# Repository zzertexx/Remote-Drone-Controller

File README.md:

# Remote Drone Controller
Remote Controller for my [Drone](https://github.com/zzertexx/drone) with FPV viewer with Phone and Control with Joystick

# How it works
My drone uses ELRS channel to Receive commands and this controller acts as Transmitter on ELRS using SX1280 module while getting joysticks commands from ESP32-C3 that sends them to ESP32-S3.

# How to use it
1. Order PCB
2. Solder all components as stated in Schematics
3. Flash [ELRS firmware](https://github.com/expresslrs/expresslrs) for the main ESP32-S3
4. Flash the companion firmware @ /firmware to the ESP32-C3
5. Power on, bind the controller to drone's ELRS receiver
6. Calibrate joystick min/center/max values.

# Why I designed it?
I designed drone recently, but I don't have controller for it, so I built one

# Bill of Materials
| Name | Quantity |
| --- | --- |
| E28-2G4M27S SX1280 module | 1 pc | 
| ESP32-S3 | 1 pc |
| ESP32-C3 | 1 pc |
| 2.4 GHz antenna  | 1 pc |
| Joystick | 2 pcs |
| TP4056 chip | 1 pc |
| FS8205A chip | 1 pc |
| DW01A chip | 1 pc |
| MT3608 5V converter | 1 pc |
| AMS1117 3.3V converter | 1 pc |
| WS2812 | 2 pcs |
| Tactile Button | 2 pcs |
| Resistors | 1K x3, 1.2K, 100, 4.7K x2, 0, 110K, 15K, 5.1K |
| Inductor 4.7uH | 1 pc |
| Capacitors | 0.1uF x2, 22uF x3, 47uF |
| LED THT D3mm | 2 pcs |
| 2400mAh Battery 18650 | 1 pc |
| Battery Holder | 1 pc |

# Next feautures
3D Enclosure
VTX Video Receiver for Phone

# Photos

# AI DISCLOSURE
AI was used for researching various components, tradeofs and their compatibility

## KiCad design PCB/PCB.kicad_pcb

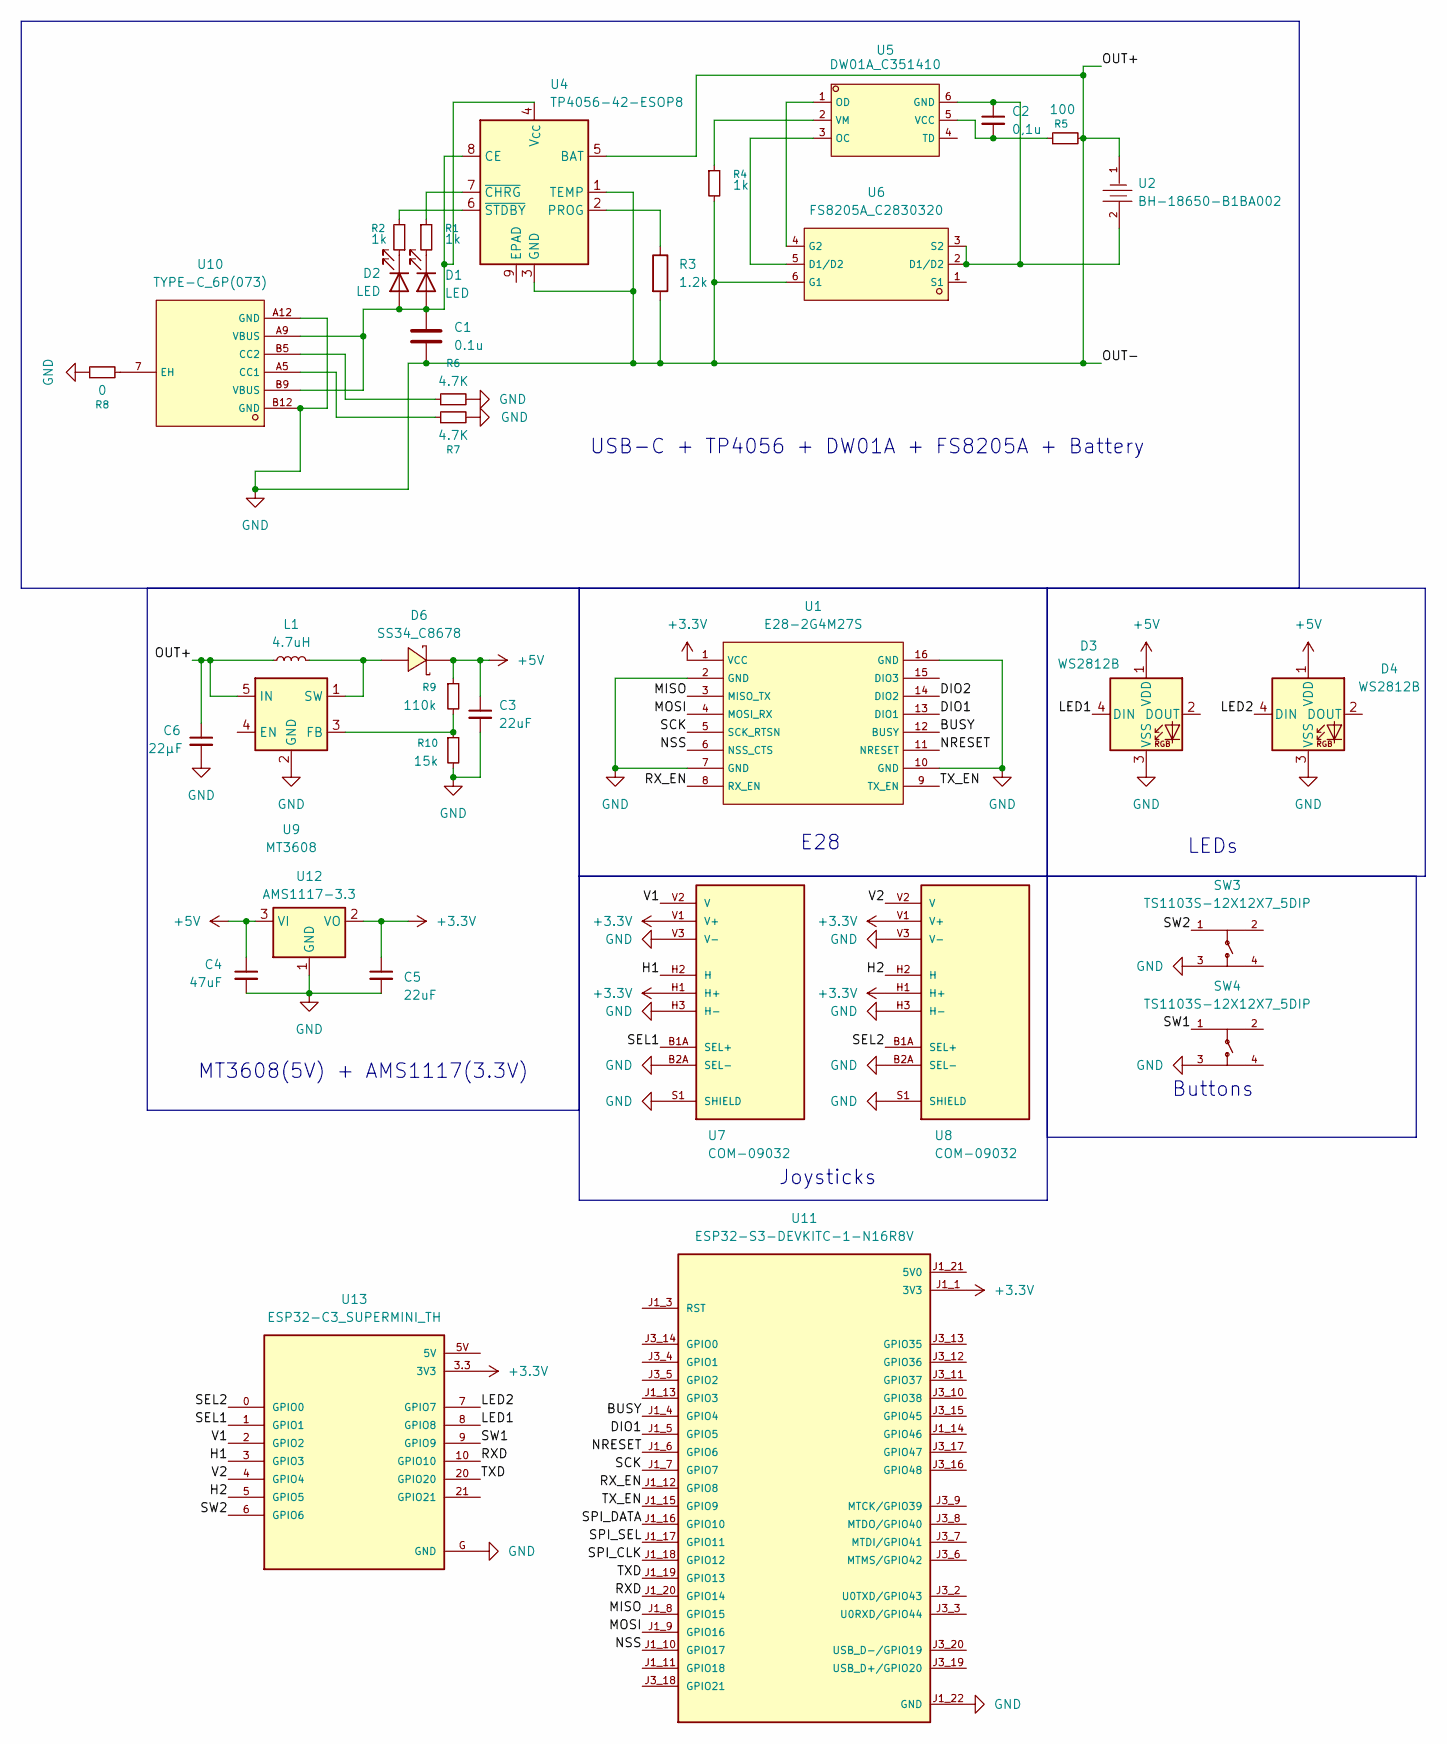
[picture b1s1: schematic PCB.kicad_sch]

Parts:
C1: 0.1u; C_0402_1005Metric
C2: 0,1u; C_0402_1005Metric
C3, C5: 22uF; C_1206_3216Metric
C4: 47uF; C_0805_2012Metric
C6: 22µF; C_1206_3216Metric
D1, D2: LED; LED_D3.0mm
D3, D4: WS2812B; LED_WS2812B_PLCC4_5.0x5.0mm_P3.2mm
D6: SS34_C8678; SMA_L4.3-W2.6-LS5.2-RD; LCSC C8678
L1: 4.7uH; C_0603_1608Metric
R1, R2, R4: 1k; C_0603_1608Metric
R3: 1.2k; C_0603_1608Metric
R5: 100; C_0603_1608Metric
R6, R7: 4.7K; C_0603_1608Metric
R8: 0; C_0603_1608Metric
R9: 110k; C_0603_1608Metric
R10: 15k; C_0603_1608Metric
SW3, SW4: TS1103S-12X12X7_5DIP; SW-TH_4P-L12.0-W12.0-P5.00-LS12.5; LCSC C48677982
U1: E28-2G4M27S; WIRELM-SMD_E28-2G4M2XS; LCSC C411312
U2: BH-18650-B1BA002; BATTERY-SMD_18650-1S-L77.1-W20.7-1; LCSC C2988620
U4: TP4056-42-ESOP8; SOIC-8-1EP_3.9x4.9mm_P1.27mm_EP2.41x3.3mm_ThermalVias
U5: DW01A_C351410; SOT-23-6_L2.9-W1.6-P0.95-LS2.8-BL; LCSC C351410
U6: FS8205A_C2830320; SOT-23-6_L2.9-W1.6-P0.95-LS2.8-BR; LCSC C2830320
U7, U8: COM-09032; XDCR_COM-09032; PARTREV N/A
U9: MT3608; SOT-23-6
U10: TYPE-C_6P(073); TYPE-C-SMD_TYPE-C-6P-073; LCSC C668623
U11: ESP32-S3-DEVKITC-1-N16R8V; XCVR_ESP32-S3-DEVKITC-1-N16R8V; PARTREV 1.1
U12: AMS1117-3.3; SOT-223-3_TabPin2
U13: ESP32-C3_SUPERMINI_TH; MODULE_ESP32-C3_SUPERMINI_TH

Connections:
+3.3V: C5.1, U1.1 (VCC), U7.H1 (H+), U7.V1 (V+), U8.H1 (H+), U8.V1 (V+), U11.J1_1 (3V3), U11.J1_2 (3V3), U12.2 (VO), U13.3.3 (3V3)
+5V: C3.1, C4.1, D3.1 (VDD), D4.1 (VDD), D6.1 (K), R9.1, U12.3 (VI)
/BUSY: U1.12 (BUSY), U11.J1_4 (GPIO4)
/DIO1: U1.13 (DIO1), U11.J1_5 (GPIO5)
/H1: U7.H2 (H), U13.3 (GPIO3); also elsewhere on the board
/H2: U8.H2 (H), U13.5 (GPIO5); also elsewhere on the board
/LED1: D3.4 (DIN), U13.8 (GPIO8); also elsewhere on the board
/LED2: D4.4 (DIN), U13.7 (GPIO7); also elsewhere on the board
/MISO: U1.3 (MISO_TX), U11.J1_8 (GPIO15)
/MOSI: U1.4 (MOSI_RX), U11.J1_9 (GPIO16)
/NRESET: U1.11 (NRESET), U11.J1_6 (GPIO6)
/NSS: U1.6 (NSS_CTS), U11.J1_10 (GPIO17)
/RXD: U11.J1_20 (GPIO14), U13.10 (GPIO10); also elsewhere on the board
/RX_EN: U1.8 (RX_EN), U11.J1_12 (GPIO8)
/SCK: U1.5 (SCK_RTSN), U11.J1_7 (GPIO7)
/SEL1: U7.B1A (SEL+), U13.1 (GPIO1); also elsewhere on the board
/SEL2: U8.B1A (SEL+), U13.0 (GPIO0); also elsewhere on the board
/SPI_CLK: U11.J1_18 (GPIO12)
/SPI_DATA: U11.J1_16 (GPIO10)
/SPI_SEL: U11.J1_17 (GPIO11)
/SW1: SW4.1, U13.9 (GPIO9); also elsewhere on the board
/SW2: SW3.1, U13.6 (GPIO6); also elsewhere on the board
/TXD: U11.J1_19 (GPIO13), U13.20 (GPIO20); also elsewhere on the board
/TX_EN: U1.9 (TX_EN), U11.J1_15 (GPIO9)
/V1: U7.V2 (V), U13.2 (GPIO2); also elsewhere on the board
/V2: U8.V2 (V), U13.4 (GPIO4); also elsewhere on the board
GND: C1.2, C3.2, C4.2, C5.2, C6.1, C6.2, D3.3 (VSS), D4.3 (VSS), L1.1, R3.2, R4.2, R5.2, R6.2, R7.2, R8.1, R10.2, SW3.3, SW4.3, U1.2 (GND), U1.7 (GND), U1.10 (GND), U1.16 (GND), U2.1, U4.1 (TEMP), U4.3 (GND), U4.5 (BAT), U6.6 (G1), U7.B2A (SEL-), U7.H3 (H-), U7.S1 (SHIELD), U7.S2 (SHIELD), U7.S3 (SHIELD), U7.S4 (SHIELD), U7.V3 (V-), U8.B2A (SEL-), U8.H3 (H-), U8.S1 (SHIELD), U8.S2 (SHIELD), U8.S3 (SHIELD), U8.S4 (SHIELD), U8.V3 (V-), U9.2 (GND), U9.5 (IN), U10.A12 (GND), U10.B12 (GND), U11.J1_22 (GND), U11.J3_1 (GND), U11.J3_21 (GND), U11.J3_22 (GND), U12.1 (GND), U13.G (GND)
unnamed: C1.1, D1.2 (A), D2.2 (A), U4.4 (V_{CC}), U4.8 (CE), U10.A9 (VBUS), U10.B9 (VBUS)
unnamed: D1.1 (K), R1.2
unnamed: D2.1 (K), R2.1
unnamed: D6.2 (A), L1.2, U9.1 (SW)
unnamed: R3.1, U4.2 (PROG)
unnamed: R1.1, U4.7 (~CHRG)
unnamed: R2.2, U4.6 (~STDBY)
unnamed: C2.1, U2.2, U5.6 (GND), U6.2 (D1/D2), U6.3 (S2)
unnamed: U5.3 (OC), U6.5 (D1/D2)
unnamed: U5.1 (OD), U6.4 (G2)
unnamed: C2.2, R5.1, U5.5 (VCC)
unnamed: R4.1, U5.2 (VM)
unnamed: R9.2, R10.1, U9.3 (FB)
unnamed: R7.1, U10.A5 (CC1)
unnamed: R6.1, U10.B5 (CC2)
unnamed: R8.2, U10.7 (EH)

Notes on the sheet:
LEDs
USB-C + TP4056 + DW01A + FS8205A + Battery
MT3608(5V) + AMS1117(3.3V)
Buttons
E28
Joysticks

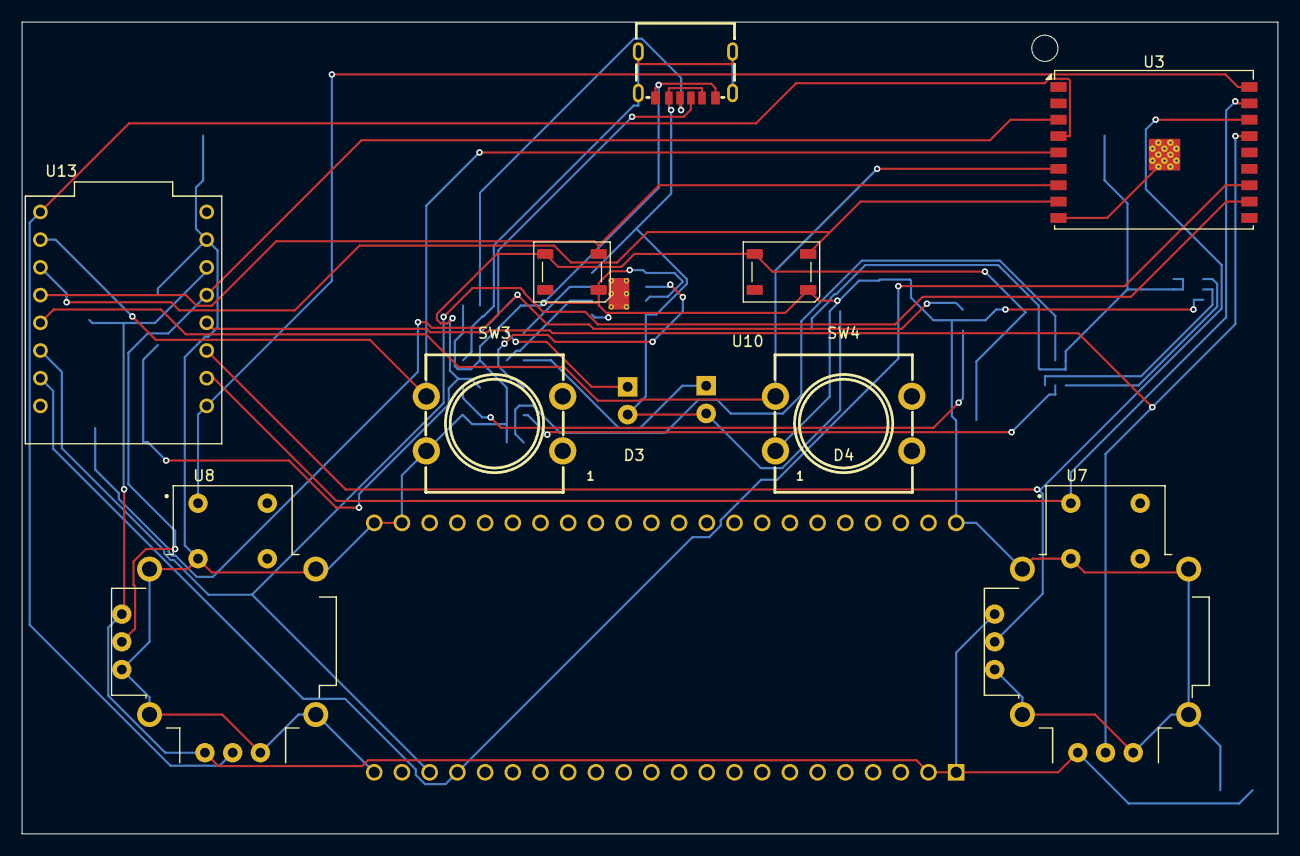
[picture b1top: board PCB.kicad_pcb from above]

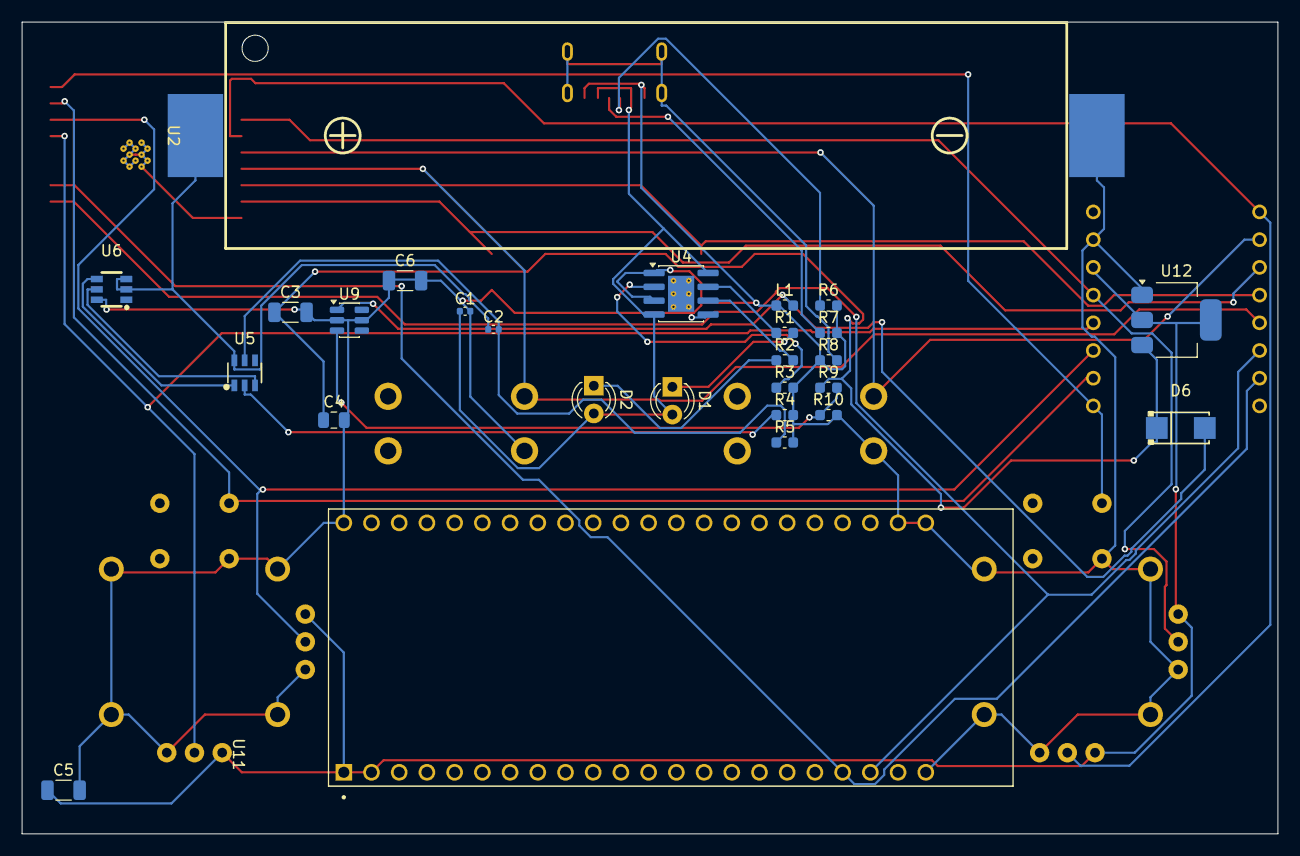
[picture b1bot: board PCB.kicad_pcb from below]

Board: 2 copper layers, 115.1 x 74.4 mm, 36 parts (27 on the bottom side), 32 nets.

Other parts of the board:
U3: ESP32-C3-WROOM-02U

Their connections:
/H1: U3.15 (IO3); also elsewhere on the board
/H2: U3.4 (IO5); also elsewhere on the board
/LED1: U3.7 (IO8); also elsewhere on the board
/LED2: U3.8 (IO9); also elsewhere on the board
/RXD: U3.11 (IO20/RXD); also elsewhere on the board
/SEL1: U3.17 (IO1); also elsewhere on the board
/SEL2: U3.18 (IO0); also elsewhere on the board
/SW1: U3.6 (IO7); also elsewhere on the board
/SW2: U3.5 (IO6); also elsewhere on the board
/TXD: U3.12 (IO21/TXD); also elsewhere on the board
/V1: U3.16 (IO2); also elsewhere on the board
/V2: U3.3 (IO4); also elsewhere on the board
unnamed: U3.9 (GND), U3.19 (GND)

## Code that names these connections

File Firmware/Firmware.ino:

#include <Adafruit_NeoPixel.h>

#define V1_PIN            0 
#define H1_PIN            1  
#define V2_PIN            2  
#define H2_PIN            3   
#define SEL2_PIN          4  
#define SW2_PIN           6  
#define LED2_PIN          7 
#define LED1_PIN          8   
#define SW1_PIN           9   
#define RXD_PIN           10  
#define TXD_PIN           20  
#define SEL1_PIN          21  

#define CRSF_BAUD         420000

#define CRSF_SYNC_BYTE                     0xC8
#define CRSF_FRAMETYPE_RC_CHANNELS_PACKED  0x16
#define CRSF_FRAMETYPE_LINK_STATISTICS     0x14
#define CRSF_CHANNEL_VALUE_MIN   172   
#define CRSF_CHANNEL_VALUE_MID   992   
#define CRSF_CHANNEL_VALUE_MAX   1811  

#define ELRS_ADDRESS          0xEE
#define ADDR_RADIO             0xEA
#define ELRS_BIND_COMMAND      0xFF
#define TYPE_SETTINGS_WRITE    0x2D

Adafruit_NeoPixel led1(1, LED1_PIN, NEO_GRB + NEO_KHZ800);
Adafruit_NeoPixel led2(1, LED2_PIN, NEO_GRB + NEO_KHZ800);

uint16_t channels[16];

uint8_t crc8_dvb_s2(uint8_t crc, uint8_t a) {
  crc ^= a;
  for (int i = 0; i < 8; i++) {
    crc = (crc & 0x80) ? (crc << 1) ^ 0xD5 : (crc << 1);
  }
  return crc;
}

uint8_t crc8_buf(uint8_t *data, uint8_t len) {
  uint8_t crc = 0;
  for (uint8_t i = 0; i < len; i++) crc = crc8_dvb_s2(crc, data[i]);
  return crc;
}

uint16_t adcToCrsf(int adcValue, int adcMin, int adcMid, int adcMax) {
  adcValue = constrain(adcValue, adcMin, adcMax);
  if (adcValue < adcMid) {
    return map(adcValue, adcMin, adcMid, CRSF_CHANNEL_VALUE_MIN, CRSF_CHANNEL_VALUE_MID);
  }
  return map(adcValue, adcMid, adcMax, CRSF_CHANNEL_VALUE_MID, CRSF_CHANNEL_VALUE_MAX);
}

void sendCrsfChannels() {
  uint8_t frame[26];
  uint8_t payload[22];
  memset(payload, 0, sizeof(payload));

  uint32_t bitBuffer = 0;
  int bitsInBuffer = 0;
  int byteIndex = 0;

  for (int ch = 0; ch < 16; ch++) {
    bitBuffer |= ((uint32_t)(channels[ch] & 0x7FF)) << bitsInBuffer;
    bitsInBuffer += 11;
    while (bitsInBuffer >= 8) {
      payload[byteIndex++] = bitBuffer & 0xFF;
      bitBuffer >>= 8;
      bitsInBuffer -= 8;
    }
  }
  if (bitsInBuffer > 0) payload[byteIndex++] = bitBuffer & 0xFF;

  frame[0] = CRSF_SYNC_BYTE;
  frame[1] = 22 + 2;
  frame[2] = CRSF_FRAMETYPE_RC_CHANNELS_PACKED;
  memcpy(&frame[3], payload, 22);
  frame[25] = crc8_buf(&frame[2], 23);

  Serial1.write(frame, 26);
}

void sendBindCommand() {
  uint8_t packet[8];
  packet[0] = ELRS_ADDRESS;
  packet[1] = 6;
  packet[2] = TYPE_SETTINGS_WRITE;
  packet[3] = ELRS_ADDRESS;
  packet[4] = ADDR_RADIO;
  packet[5] = ELRS_BIND_COMMAND;
  packet[6] = 0x01;
  packet[7] = crc8_buf(&packet[2], 5);
  Serial1.write(packet, 8);
}

void updatePowerLED() {
  led1.setPixelColor(0, led1.Color(40, 40, 40));
  led1.show();
}

volatile bool droneConnected = false;
volatile unsigned long lastTelemetryMillis = 0;
#define TELEMETRY_TIMEOUT_MS 1000

void updateConnectionLED() {
  bool connected = droneConnected && (millis() - lastTelemetryMillis < TELEMETRY_TIMEOUT_MS);
  led2.setPixelColor(0, connected ? led2.Color(0, 255, 0) : led2.Color(255, 0, 0));
  led2.show();
}

uint8_t rxBuf[64];
uint8_t rxIndex = 0;

void pollCrsfTelemetry() {
  while (Serial1.available()) {
    uint8_t b = Serial1.read();
    if (rxIndex == 0 && b != CRSF_SYNC_BYTE) continue;
    rxBuf[rxIndex++] = b;

    if (rxIndex >= 2) {
      uint8_t frameLen = rxBuf[1];
      if (rxIndex >= frameLen + 2) {
        uint8_t expectedCrc = rxBuf[frameLen + 1];
        uint8_t actualCrc = crc8_buf(&rxBuf[2], frameLen - 1);
        if (expectedCrc == actualCrc && rxBuf[2] == CRSF_FRAMETYPE_LINK_STATISTICS) {
          droneConnected = true;
          lastTelemetryMillis = millis();
        }
        rxIndex = 0;
      }
    }
    if (rxIndex >= sizeof(rxBuf)) rxIndex = 0;
  }
}

bool lastSW2State = HIGH;
bool lastSW1State = HIGH;
unsigned long sw1PressStart = 0;
#define SW1_LONGPRESS_MS 1500

void handleButtons() {
  bool sw2State = digitalRead(SW2_PIN);
  if (sw2State == LOW && lastSW2State == HIGH) {
    sendBindCommand();
  }
  lastSW2State = sw2State;

  bool sw1State = digitalRead(SW1_PIN);
  if (sw1State == LOW && lastSW1State == HIGH) {
    sw1PressStart = millis();
  }
  if (sw1State == LOW && (millis() - sw1PressStart > SW1_LONGPRESS_MS)) {
    led1.setPixelColor(0, 0); led1.show();
    led2.setPixelColor(0, 0); led2.show();
    gpio_wakeup_enable((gpio_num_t)SW1_PIN, GPIO_INTR_LOW_LEVEL);
    esp_sleep_enable_gpio_wakeup();
    esp_deep_sleep_start();
  }
  lastSW1State = sw1State;

  channels[6] = (digitalRead(SEL1_PIN) == LOW) ? CRSF_CHANNEL_VALUE_MAX : CRSF_CHANNEL_VALUE_MIN;
  channels[7] = (digitalRead(SEL2_PIN) == LOW) ? CRSF_CHANNEL_VALUE_MAX : CRSF_CHANNEL_VALUE_MIN;
}

void readJoysticks() {
  int adcMin = 100, adcMid = 2048, adcMax = 3995;

  int v1Raw = analogRead(V1_PIN);
  int h1Raw = analogRead(H1_PIN);
  int v2Raw = analogRead(V2_PIN);
  int h2Raw = analogRead(H2_PIN);

  channels[0] = adcToCrsf(h2Raw, adcMin, adcMid, adcMax); 
  channels[1] = adcToCrsf(v2Raw, adcMin, adcMid, adcMax); 
  channels[2] = adcToCrsf(v1Raw, adcMin, adcMid, adcMax); 
  channels[3] = adcToCrsf(h1Raw, adcMin, adcMid, adcMax); 
}

void setup() {
  Serial1.begin(CRSF_BAUD, SERIAL_8N1, RXD_PIN, TXD_PIN);

  pinMode(SW1_PIN, INPUT_PULLUP);
  pinMode(SW2_PIN, INPUT_PULLUP);
  pinMode(SEL1_PIN, INPUT_PULLUP);
  pinMode(SEL2_PIN, INPUT_PULLUP);

  led1.begin();
  led2.begin();
  led1.setBrightness(80);
  led2.setBrightness(80);
  led1.show();
  led2.show();

  for (int i = 0; i < 16; i++) channels[i] = CRSF_CHANNEL_VALUE_MID;
}

unsigned long lastChannelSend = 0;
#define CHANNEL_SEND_INTERVAL_MS 4 

void loop() {
  pollCrsfTelemetry();
  handleButtons();
  readJoysticks();

  if (millis() - lastChannelSend >= CHANNEL_SEND_INTERVAL_MS) {
    sendCrsfChannels();
    lastChannelSend = millis();
  }

  updatePowerLED();
  updateConnectionLED();
}
